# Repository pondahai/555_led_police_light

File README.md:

# 555_led_police_light

## 電路模擬：
https://www.falstad.com/circuit/circuitjs.html?ctz=CQAgjCAMB0l3BWEAmaA2AHBg7GgzAJyRoAsJa2CyIpI2ICkDApgLRhgBQA7iAWiHYD+4AZB58BYKWibSonAMaTRKjEw2x4kCGHR5MGCmjQJGHE1C1cA5mqYiRGzgCcVQ9+qggS2OBJF2MhRkEkEwYPEAJXcIsNogsI0fJjxvTQROAHkQPANBEgwUplZC9M5pJGkSjmowXHCwagFUImxsAmwyPGRkHBIqCV6wxJQscMih8dG+otYvcV48gVKi2YKi8TdAr0C4719-Xn2PavCxTjtkBAEy64FaZ149qWCPRdES3ZWFiTOwAjUEQA6gfET3cDBCHiK43XLIJgQ5blY5QuFnaGuFQg7F9A5+D7I4ZjNahBS8dZNNbjHEfYlUkngPHiSqfNn1GRMMSwQEI67IXAEHoIPDkbIMBrE0iIsnOGLAvG0BnJEipdJWTLPKR4+nMrHguHAwH4-x2ER4KgqAybBTKcHjc2WuRabSu7RgNj0PRoaSqvAErCkAgkAhWOBcLWMjHjMEtQ0tGNY5GrXL5MpyFloajIspEsnUAAmzAAZgBDACuABsAC6sSvMAvgdUwHQSPNhPAYMLEwldkJhEg9fsKaTUKiksLjnxrEBFstV2v1xsQZItiO5Pu5tObCSD6jEwoypK7rzEqc9ipZjcDoqd7v52clis1usNpur2BcUc+IdlPfDwsnwXV9l2bT9L2oQ9hygu5H3nF8l3fdJwKWTcin-dNd1-dCvEw3gYKKKc8IYHUyQQSVZQgiUWjIhpYLnZ9FzfFdkNbXhyNuQi8UwgB7FB4QOSACFDJAWzgbAMCaUT+OzTg+K9MQfDAYgGDDeBOlMLMqnAOSUBkA5lLHKwIDqXTRVUJgSGUkzoFE6AIDSbMO04IA

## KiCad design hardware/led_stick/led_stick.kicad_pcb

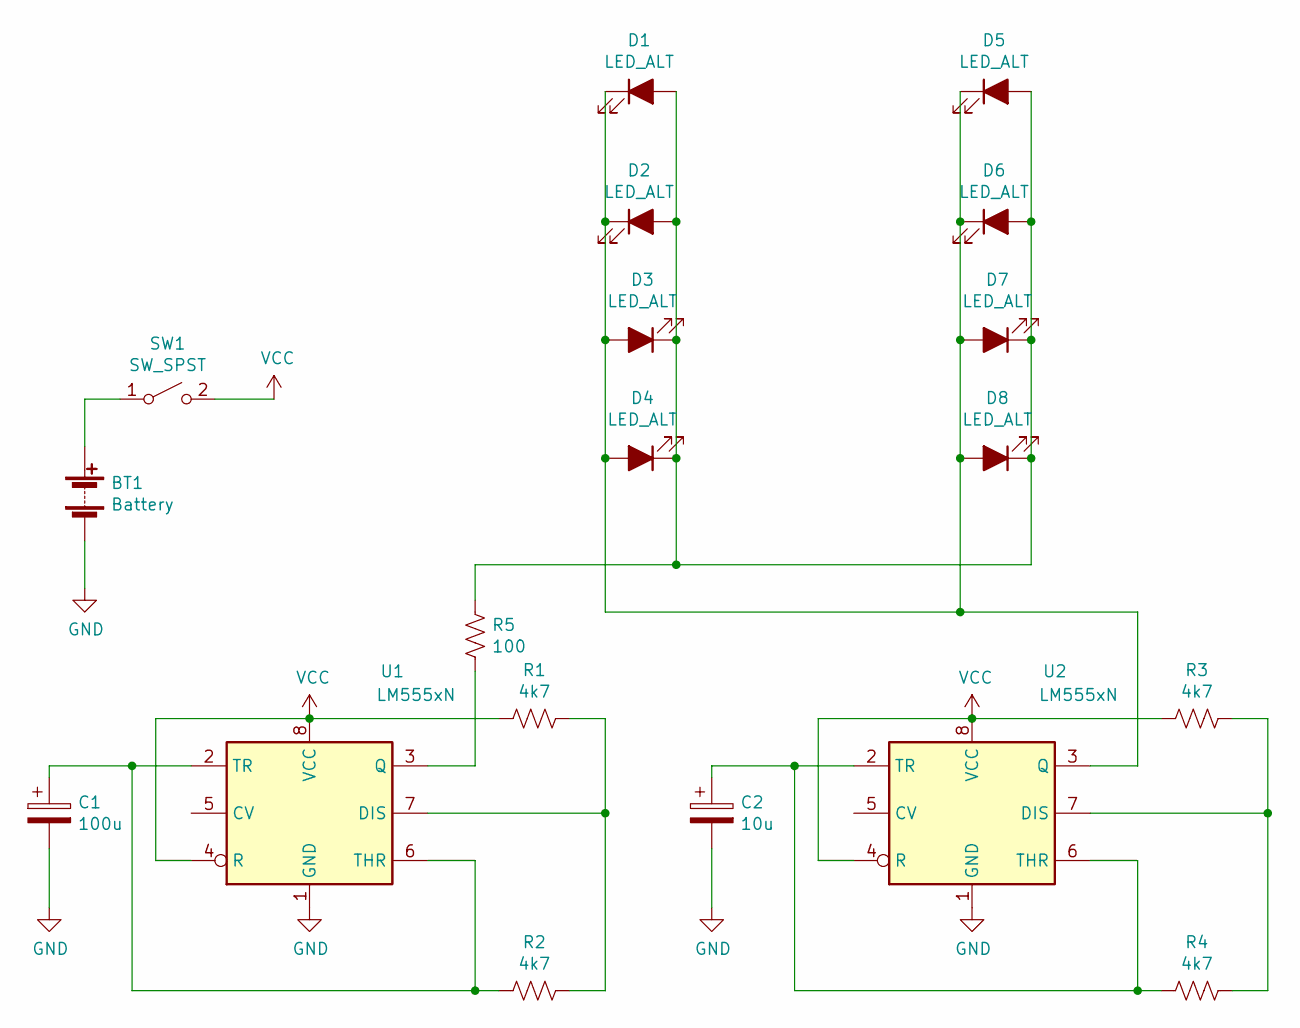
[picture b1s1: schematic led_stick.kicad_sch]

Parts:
BT1: Battery; PhoenixContact_MCV_1,5_2-G-3.5_1x02_P3.50mm_Vertical
C1: 100u; CP_Radial_D5.0mm_P2.00mm
C2: 10u; CP_Radial_D5.0mm_P2.00mm
D1, D2, D3, D4, D5, D6, D7, D8: LED_ALT; LED_D8.0mm
R1, R2, R3, R4: 4k7; R_Axial_DIN0309_L9.0mm_D3.2mm_P15.24mm_Horizontal
R5: 100; R_Axial_DIN0309_L9.0mm_D3.2mm_P15.24mm_Horizontal
SW1: SW_SPST; SW_E-Switch_EG1224_SPDT_Angled
U1, U2: LM555xN; DIP-8_W7.62mm

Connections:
GND: BT1.2 (-), C1.2, C2.2, U1.1 (GND), U2.1 (GND)
unnamed: BT1.1 (+), SW1.1 (A)
unnamed: C1.1, R2.2, U1.2 (TR), U1.6 (THR)
unnamed: C2.1, R4.2, U2.2 (TR), U2.6 (THR)
unnamed: D1.1 (K), D2.1 (K), D3.2 (A), D4.2 (A), D5.1 (K), D6.1 (K), D7.2 (A), D8.2 (A), U2.3 (Q)
unnamed: D1.2 (A), D2.2 (A), D3.1 (K), D4.1 (K), D5.2 (A), D6.2 (A), D7.1 (K), D8.1 (K), R5.2
unnamed: R1.1, R2.1, U1.7 (DIS)
unnamed: R3.1, R4.1, U2.7 (DIS)
unnamed: R5.1, U1.3 (Q)
VCC: R1.2, R3.2, SW1.2 (B), U1.4 (R), U1.8 (VCC), U2.4 (R), U2.8 (VCC)

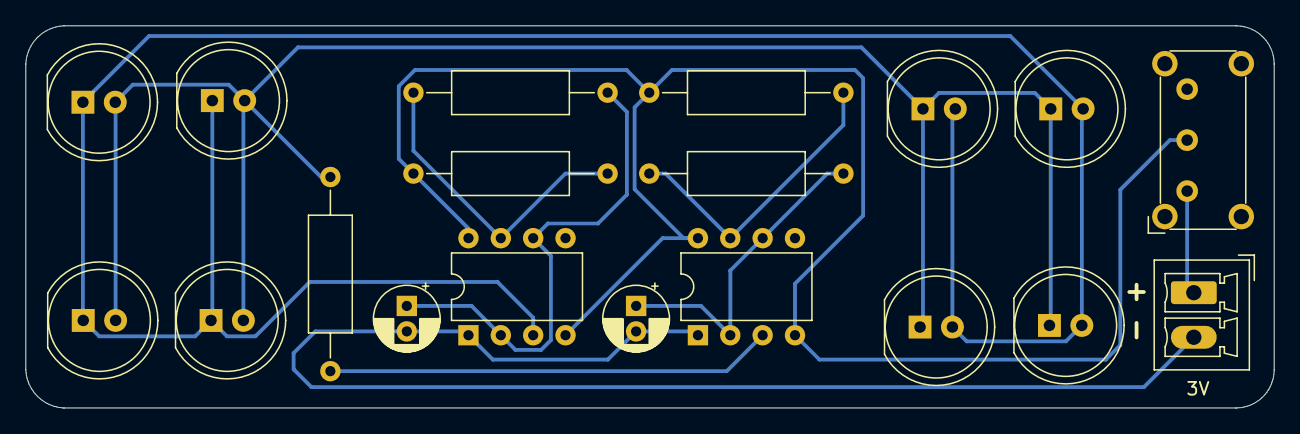
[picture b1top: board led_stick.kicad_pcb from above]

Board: 2 copper layers, 98.0 x 30.0 mm, 19 parts (0 on the bottom side), 10 nets.
